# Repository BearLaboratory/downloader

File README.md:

# <center>Downloader</center>
> 一个便宜且兼容ESP系列芯片自动烧录的USB-TTL硬件工具

<p align="center">

</p>

## 方便使用烧录夹具进行下载

## 基于CH340K抛弃价格昂贵的CP102系列芯片

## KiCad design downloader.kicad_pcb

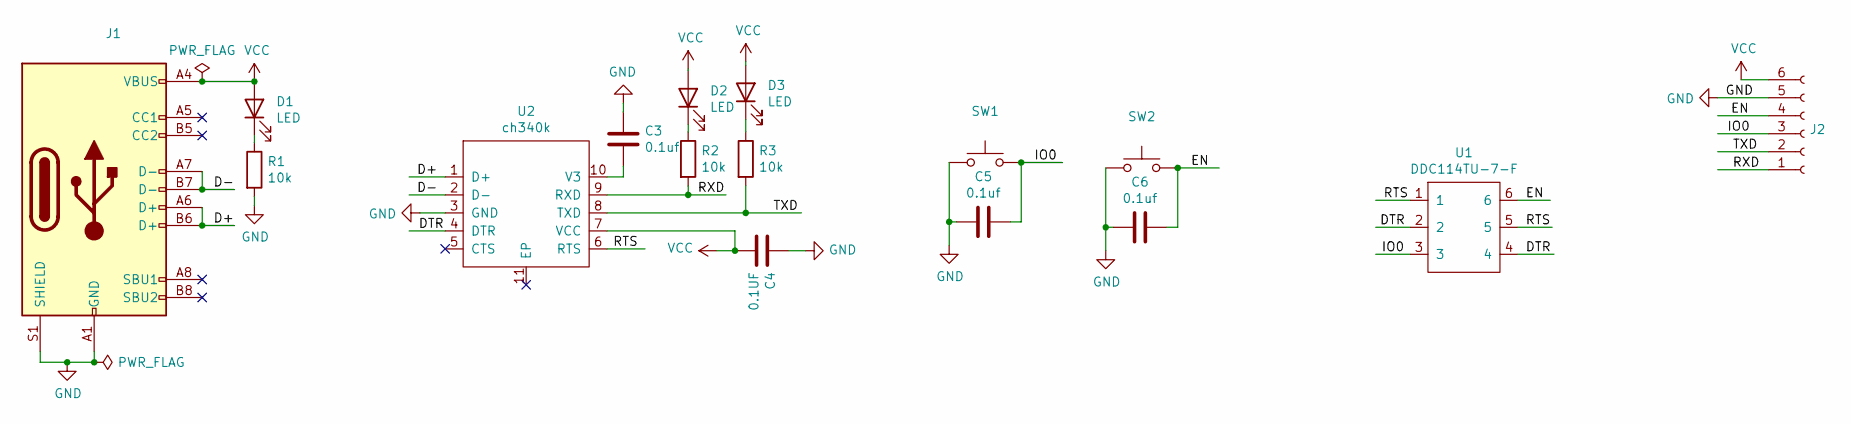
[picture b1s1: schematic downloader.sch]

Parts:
C3, C5, C6: 0.1uf; C_0603_1608Metric
C4: 0.1UF; C_0603_1608Metric
D1, D2, D3: LED; D_0603_1608Metric
J1: USB_C_Receptacle_USB2.0; USB_C_Receptacle_HRO_TYPE-C-31-M-12
J2: Conn_01x06_Female; PinHeader_1x06_P2.00mm_Horizontal
R1, R2, R3: 10k; R_0603_1608Metric
SW1, SW2: SW_Push; bt-342
U1: DDC114TU-7-F; SOT-363_SC-70-6
U2: ch340k; ESSOP-10_3.9x4.9mm_P1.00mm

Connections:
/D+: J1.A6 (D+), J1.B6 (D+), U2.1 (D+)
/D-: J1.A7 (D-), J1.B7 (D-), U2.2 (D-)
/DTR: U1.2, U1.4, U2.4 (DTR)
/EN: C6.1, J2.4, SW2.2, U1.6
/IO0: C5.1, J2.3, SW1.2, U1.3
/RTS: U1.1, U1.5, U2.6 (RTS)
/RXD: J2.1, R2.2, U2.9 (RXD)
/TXD: J2.2, R3.2, U2.8 (TXD)
GND: C3.1, C4.1, C5.2, C6.2, J1.A1 (GND), J1.A12 (GND), J1.B1 (GND), J1.B12 (GND), J1.S1 (SHIELD), J2.5, R1.2, SW1.1, SW2.1, U2.3 (GND)
unnamed: C3.2, U2.10 (V3)
unnamed: D1.1 (K), R1.1
unnamed: D2.1 (K), R2.1
unnamed: D3.1 (K), R3.1
VCC: C4.2, D1.2 (A), D2.2 (A), D3.2 (A), J1.A4 (VBUS), J1.A9 (VBUS), J1.B4 (VBUS), J1.B9 (VBUS), J2.6, U2.7 (VCC)

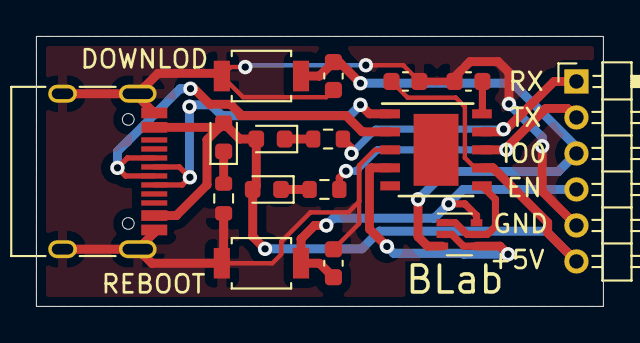
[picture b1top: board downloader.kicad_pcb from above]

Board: 2 copper layers, 31.5 x 15.0 mm, 16 parts (0 on the bottom side), 14 nets.

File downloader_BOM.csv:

"Comment","Description","Designator","Footprint","LibRef","Pins","Quantity","PartNumber","url",
"0.1UF","desc","C4,","C_0603_1608Metric","libref","2","1","","",
"0.1uf","desc","C6,C5,C3,","C_0603_1608Metric","libref","2","3","","",
"LED","desc","D3,D2,D1,","D_0603_1608Metric","libref","2","3","","",
"10k","desc","R3,R2,R1,","R_0603_1608Metric","libref","2","3","","",
"SW_Push","desc","SW2,SW1,","bt-342","libref","2","2","","",
"DDC114TU-7-F","desc","U1,","SOT-363_SC-70-6","libref","6","1","","",
"ch340k","desc","U2,","ESSOP-10_3.9x4.9mm_P1.00mm","libref","11","1","","",
"Through Hole Items ",
"USB_C_Receptacle_USB2.0","desc","J1,","USB_C_Receptacle_HRO_TYPE-C-31-M-12","libref","22","1","","",
"Conn_01x06_Female","desc","J2,","PinHeader_1x06_P2.00mm_Horizontal","libref","6","1","","",

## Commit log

2020-12-30 init
2020-12-30 add readme
2021-01-21 v1.0
2021-01-21 Create LICENSE
2021-05-22 version2.0
2021-06-09 ❤❤1.0完整验证
2021-07-04 😀😀更新图片
2021-07-04 修改readme

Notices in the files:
README.md:
License: GPL
